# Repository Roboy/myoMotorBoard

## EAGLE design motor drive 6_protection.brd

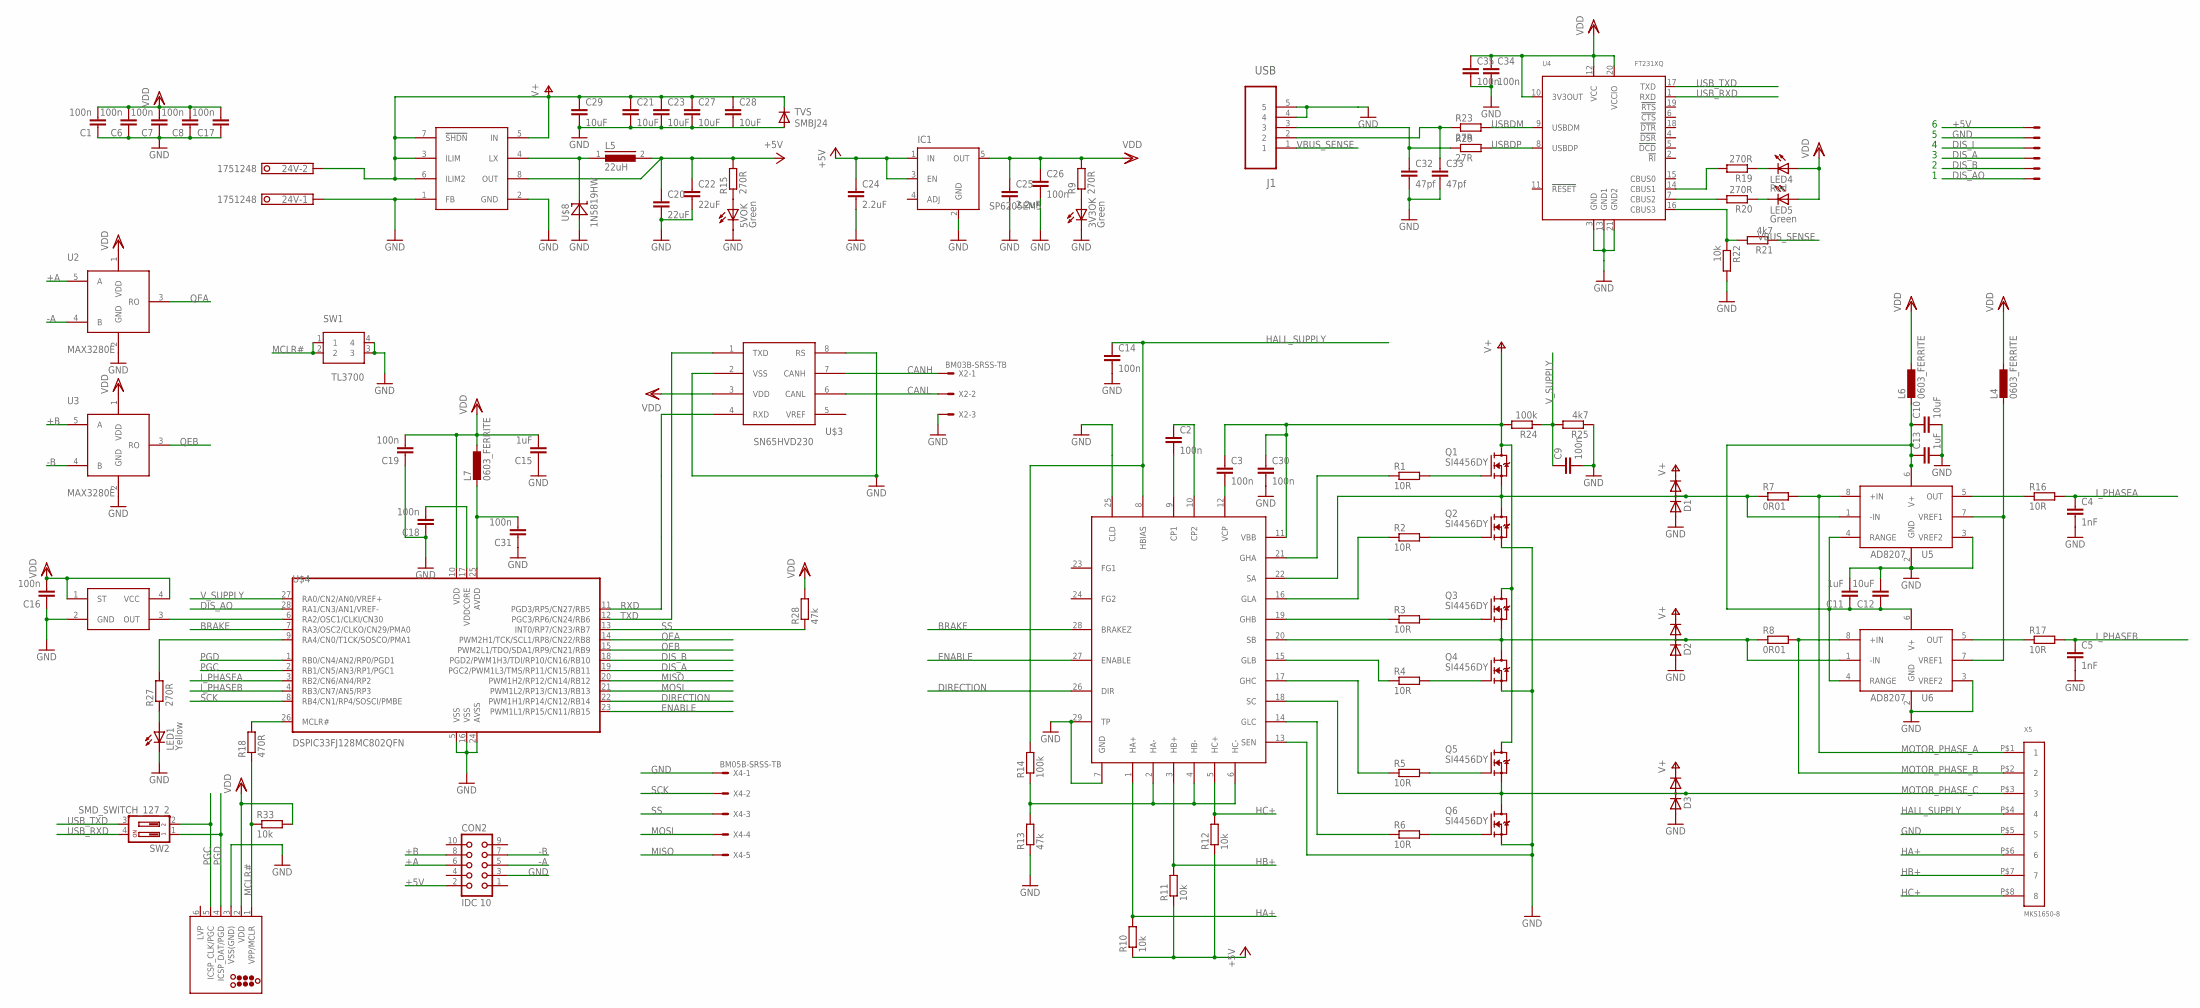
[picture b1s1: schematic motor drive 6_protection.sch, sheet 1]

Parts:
3V3OK, 5VOK: Green; CHIPLED_0603
24V: 1751248
C1, C2, C3, C6, C7, C8, C9, C14, C16, C17, C18, C19, C26, C30, C31, C34, C35: 100n; C0402K
C4, C5: 1nF; C0402K
C10, C12: 10uF; C0805K
C11, C13, C15: 1uF; C0603K
C20, C22: 22uF; C1210
C21, C23, C27, C28, C29: 10uF; C1210
C24, C25: 2.2uF; C1210
C32, C33: 47pf; C0402K
CON2: IDC 10; CON10
D1, D2, D3: DIODE_2CACA-SOT23; SOT23
IC1: SP6205EM5; SOT23-5
J1: USB; MOLEX_47346-0001
J3: TAG Connect; TC2030-MCP-NL
L4, L6, L7: 0603_FERRITE; R0603
L5: 22uH; DR73
LED1: Yellow; CHIPLED_0603
LED4: Red; CHIPLED_0603
LED5: Green; CHIPLED_0603
Q1, Q2, Q3, Q4, Q5, Q6: SI4456DY; SO8
R1, R2, R3, R4, R5, R6, R16, R17: 10R; R0603
R7, R8: 0R01; R2512
R9, R15, R19, R20, R27: 270R; R0402
R10, R11, R12, R22, R33: 10k; R0402
R13, R28: 47k; R0402
R14, R24: 100k; R0402
R18: 470R; R0402
R21, R25: 4k7; R0402
R23, R29: 27R; R0402
SW1: TL3700
SW2: SMD_SWITCH_127_2
TVS: SMBJ24; SOD-123_MINI-SMA
U1: A4931; QFN-28-NEW
U2, U3: MAX3280E; SOT23-5L
U4: FT231XQ; QFN20
U5, U6: AD8207; SO8
U$3: SN65HVD230; 999
U$4: DSPIC33FJ128MC802QFN; QFN-S28-6X6
U$5: MAX1776; UMAX8
U$6: SG-310
U$8: 1N5819HW; SOD123
X1: BM06B-SRSS-TB
X2: BM03B-SRSS-TB
X4: BM05B-SRSS-TB
X5: MKS1650-8; MKS1650

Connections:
+5V: C20.1, C22.1, C24.1, CON2.2, IC1.1 (IN), IC1.3 (EN), L5.2, R10.1, R11.1, R12.1, R15.2, U$5.8 (OUT), X1.1
+A: CON2.6, U2.5 (A)
+B: CON2.8, U3.5 (A)
-A: CON2.5, U2.4 (B)
-B: CON2.7, U3.4 (B)
BRAKE: U1.28 (BRAKEZ), U$4.7 (RA3/OSC2/CLKO/CN29/PMA0)
CANH: U$3.7 (CANH), X2.1
CANL: U$3.6 (CANL), X2.2
DIRECTION: U1.26 (DIR), U$4.22 (PWM1H1/RP14/CN12/RB14)
DIS_A: U$4.19 (PGC2/PWM1L3/TMS/RP11/CN15/RB11), X1.4
DIS_AO: U$4.28 (RA1/CN3/AN1/VREF-), X1.6
DIS_B: U$4.18 (PGD2/PWM1H3/TDI/RP10/CN16/RB10), X1.5
DIS_I: X1.3
ENABLE: U1.27 (ENABLE), U$4.23 (PWM1L1/RP15/CN11/RB15)
GND: 3V3OK.C, 5VOK.C, 24V.1, C1.1, C4.2, C5.2, C6.1, C7.1, C8.1, C9.2, C10.2, C11.2, C12.2, C13.2, C14.2, C15.1, C16.1, C17.1, C18.1, C19.1, C20.2, C21.2, C22.2, C23.2, C24.2, C25.2, C26.2, C27.2, C28.2, C29.2, C30.2, C31.1, C32.2, C33.2, C34.2, C35.2, CON2.3, D1.1 (A), D2.1 (A), D3.1 (A), IC1.2 (GND), J1.4, J1.5, J3.3 (VSS(GND)), LED1.C, Q2.1 (S), Q2.2 (S), Q2.3 (S), Q4.1 (S), Q4.2 (S), Q4.3 (S), Q6.1 (S), Q6.2 (S), Q6.3 (S), R13.1, R22.2, R25.1, SW1.3, SW1.4, TVS.A, U1.7 (GND), U1.13 (SEN), U1.25 (CLD), U1.29 (TP), U2.2 (GND), U3.2 (GND), U4.3 (GND), U4.13 (GND1), U4.21 (GND2), U5.2 (GND), U5.3 (VREF2), U6.2 (GND), U6.3 (VREF2), U$3.2 (VSS), U$3.8 (RS), U$4.5 (VSS), U$4.16 (VSS), U$4.24 (AVSS), U$5.1 (FB), U$5.2 (GND), U$6.2 (GND), U$8.A, X1.2, X2.3, X4.1, X5.P$5 (5); also elsewhere on the board
HA+: R10.2, U1.1 (HA+), X5.P$6 (6)
HALL_SUPPLY: C14.1, R14.2, U1.8 (HBIAS), X5.P$4 (4)
HB+: R11.2, U1.3 (HB+), X5.P$7 (7)
HC+: R12.2, U1.5 (HC+), X5.P$8 (8)
I_PHASEA: C4.1, R16.2, U$4.3 (RB2/CN6/AN4/RP2)
I_PHASEB: C5.1, R17.2, U$4.4 (RB3/CN7/AN5/RP3)
MCLR#: J3.1 (VPP/MCLR), R18.1, R33.1, SW1.1, SW1.2
MISO: U$4.20 (PWM1H2/RP12/CN14/RB12), X4.5
MOSI: U$4.21 (PWM1L2/RP13/CN13/RB13), X4.4
MOTOR_PHASE_A: R7.2, U5.8 (+IN), X5.P$1 (1)
MOTOR_PHASE_B: R8.2, U6.8 (+IN), X5.P$2 (2)
MOTOR_PHASE_C: D3.3 (AC), Q5.1 (S), Q5.2 (S), Q5.3 (S), Q6.5 (D), Q6.6 (D), Q6.7 (D), Q6.8 (D), U1.18 (SC), X5.P$3 (3)
unnamed: Q1.4 (G), R1.2
unnamed: Q2.4 (G), R2.2
unnamed: Q3.4 (G), R3.2
unnamed: Q4.4 (G), R4.2
unnamed: Q5.4 (G), R5.2
unnamed: Q6.4 (G), R6.2
unnamed: 5VOK.A, R15.1
unnamed: R1.1, U1.21 (GHA)
unnamed: R2.1, U1.16 (GLA)
unnamed: R3.1, U1.19 (GHB)
unnamed: R4.1, U1.15 (GLB)
unnamed: R5.1, U1.17 (GHC)
unnamed: R6.1, U1.14 (GLC)
unnamed: C10.1, C11.1, C12.1, C13.1, L6.2, U5.4 (RANGE), U5.6 (V+), U6.4 (RANGE), U6.6 (V+)
unnamed: 3V3OK.A, R9.1
unnamed: LED4.C, R19.1
unnamed: U$4.6 (RA2/OSC1/CLKI/CN30), U$6.3 (OUT)
unnamed: L4.2, U5.7 (VREF1), U6.7 (VREF1)
unnamed: R18.2, U$4.26 (MCLR#)
unnamed: LED5.C, R20.1
unnamed: LED1.A, R27.1
unnamed: C18.2, U$4.17 (VDDCORE)
unnamed: R13.2, R14.1, U1.2 (HA-), U1.4 (HB-), U1.6 (HC-)
unnamed: R27.2, U$4.9 (RA4/CN0/T1CK/SOSCO/PMA1)
unnamed: R20.2, U4.7 (CBUS2)
unnamed: R19.2, U4.14 (CBUS1)
unnamed: C33.1, J1.2, R23.1
unnamed: L5.1, U$5.4 (LX), U$8.C
unnamed: R21.2, R22.1, U4.16 (CBUS3)
unnamed: C2.2, U1.9 (CP1)
unnamed: C2.1, U1.10 (CP2)
unnamed: C3.2, U1.12 (VCP)
unnamed: C32.1, J1.3, R29.1
unnamed: C31.2, L7.2, U$4.25 (AVDD)
PGC: J3.5 (ICSP_CLK/PGC), SW2.2, U$4.2 (RB1/CN5/AN3/RP1/PGC1)
PGD: J3.4 (ICSP_DAT/PGD), SW2.1, U$4.1 (RB0/CN4/AN2/RP0/PGD1)
PHASE_A: R16.1, U5.5 (OUT)
PHASE_B: R17.1, U6.5 (OUT)
QEA: U2.3 (RO), U$4.14 (PWM2H1/TCK/SCL1/RP8/CN22/RB8)
QEB: U3.3 (RO), U$4.15 (PWM2L1/TDO/SDA1/RP9/CN21/RB9)
RXD: U$3.4 (RXD), U$4.11 (PGD3/RP5/CN27/RB5)
SA: D1.3 (AC), Q1.1 (S), Q1.2 (S), Q1.3 (S), Q2.5 (D), Q2.6 (D), Q2.7 (D), Q2.8 (D), R7.1, U1.22 (SA), U5.1 (-IN)
SB: D2.3 (AC), Q3.1 (S), Q3.2 (S), Q3.3 (S), Q4.5 (D), Q4.6 (D), Q4.7 (D), Q4.8 (D), R8.1, U1.20 (SB), U6.1 (-IN)
SCK: U$4.8 (RB4/CN1/RP4/SOSCI/PMBE), X4.2
SS: R28.1, U$4.13 (INT0/RP7/CN23/RB7), X4.3
TXD: U$3.1 (TXD), U$4.12 (PGC3/RP6/CN24/RB6)
USBDM: R23.2, U4.9 (USBDM)
USBDP: R29.2, U4.8 (USBDP)
USB_RXD: SW2.4, U4.1 (RXD)
USB_TXD: SW2.3, U4.17 (TXD)
V+: 24V.2, C3.1, C21.1, C23.1, C27.1, C28.1, C29.1, C30.1, D1.2 (C), D2.2 (C), D3.2 (C), Q1.5 (D), Q1.6 (D), Q1.7 (D), Q1.8 (D), Q3.5 (D), Q3.6 (D), Q3.7 (D), Q3.8 (D), Q5.5 (D), Q5.6 (D), Q5.7 (D), Q5.8 (D), R24.2, TVS.C, U1.11 (VBB), U$5.3 (ILIM), U$5.5 (IN), U$5.6 (ILIM2), U$5.7 (!SHDN)
VBUS_SENSE: J1.1, R21.1
VDD: C1.2, C6.2, C7.2, C8.2, C15.2, C16.2, C17.2, C19.2, C25.1, C26.1, C34.1, C35.1, IC1.5 (OUT), J3.2 (VDD), L4.1, L6.1, L7.1, LED4.A, LED5.A, R9.2, R28.2, R33.2, U2.1 (VDD), U3.1 (VDD), U4.10 (3V3OUT), U4.12 (VCC), U4.20 (VCCIO), U$3.3 (VDD), U$4.10 (VDD), U$6.1 (ST), U$6.4 (VCC)
V_SUPPLY: C9.1, R24.1, R25.2, U$4.27 (RA0/CN2/AN0/VREF+)

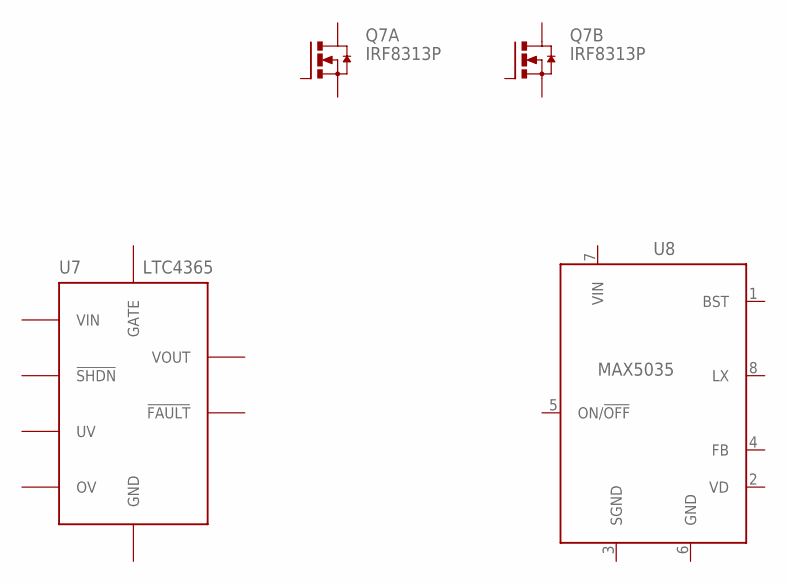
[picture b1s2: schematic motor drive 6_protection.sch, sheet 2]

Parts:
Q7: IRF8313P; SO-08
U7: LTC4365; TSOT-23-8
U8: MAX5035; SOIC8

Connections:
GND: U7.4 (GND), U8.6 (GND); also elsewhere on the board
SGND: U8.3 (SGND)
VIN: U8.7 (VIN)
VOUT: U7.7 (VOUT)

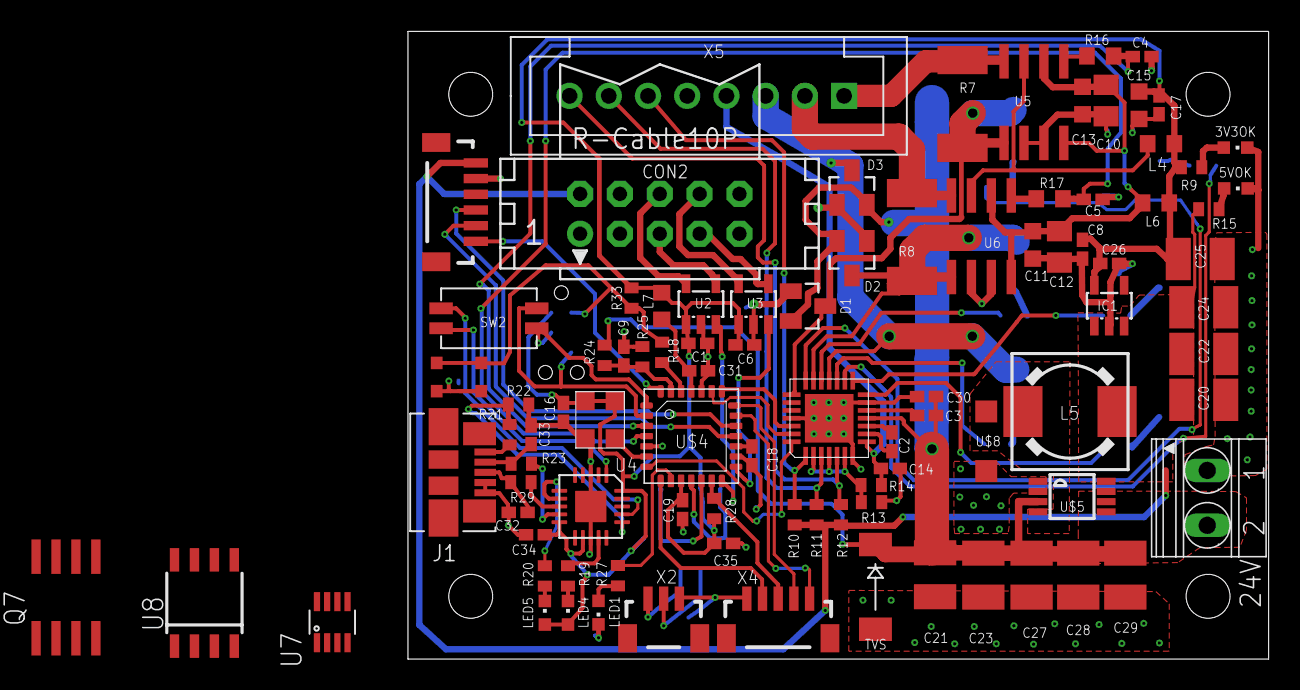
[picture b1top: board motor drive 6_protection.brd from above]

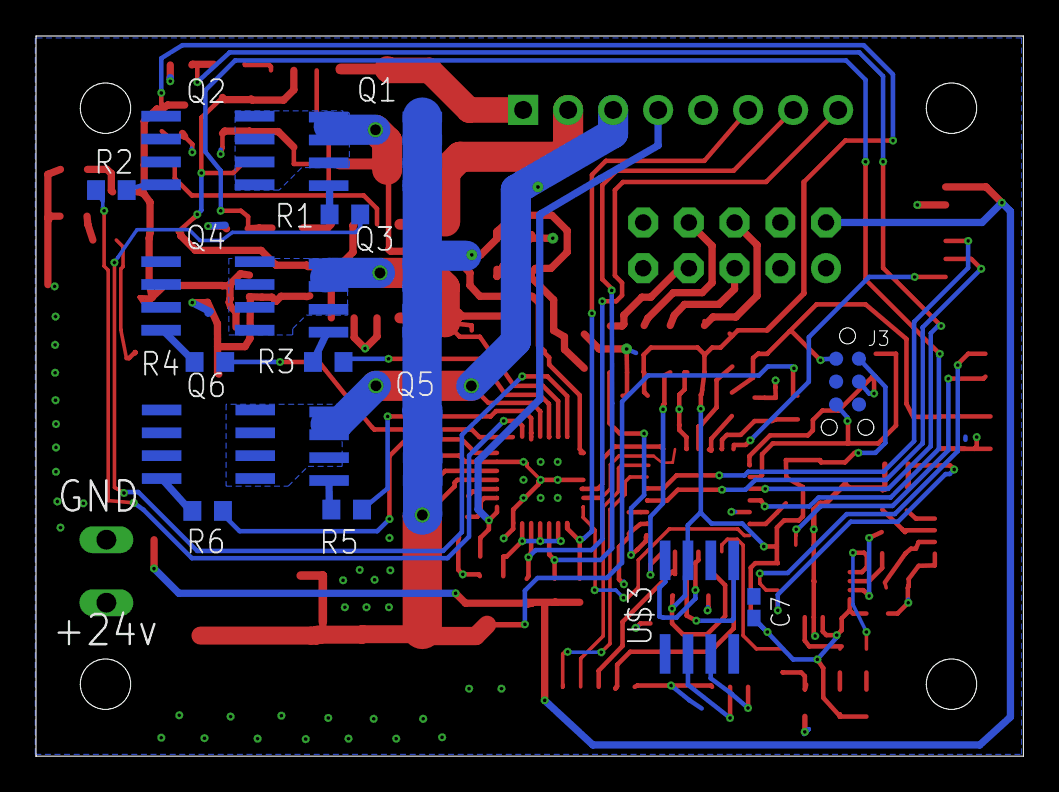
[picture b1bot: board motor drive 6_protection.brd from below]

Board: 2 copper layers, 54.9 x 40.0 mm, 108 parts (15 on the bottom side), 80 nets.

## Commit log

2019-08-27 converted to kicad

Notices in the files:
parts and their libraries:
tag-connect: ©2009 ROFA.cz - modified and updated by Robert Darlington ‹rdarlington@gmail.com›
Volks73-LinearTechnology: Creative Commons Attribution-ShareAlike 3.0 Unported (CC BY-SA 3.0), http://creativecommons.org/licenses/by-sa/3.0/.
